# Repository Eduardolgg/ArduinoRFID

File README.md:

# ArduinoRFID
RFID authentication with Arduino.

# Domoticz

## Configuration

1. Set a static IP for the ESP-01s on your router.

2. Create the user variables rfid_id y rfid_ids_valid.
* rfid_id will contain the last tag sent to Domoticz.
* rfid_ids_valid will contain all valid tags.

3 Create the scripts using those found in the Domoticz_scripts directory, replace in the scripts the static IP associated with your wifi module.

## Add a new Tag

1. Scan the tag.

2. Go to Domoticz log and copy the ID.

3. Enter it in the user variable rfid_ids_valid by separating each Id by : (Ej: IDTAG1:IDTAG2:...).

# Arduino

1. Remember to replace the Domoticz IP and the user variable ID rfid_id in the code.

2. Flash Arduino and ESP-01s

3. Make the circuit using the included schemes

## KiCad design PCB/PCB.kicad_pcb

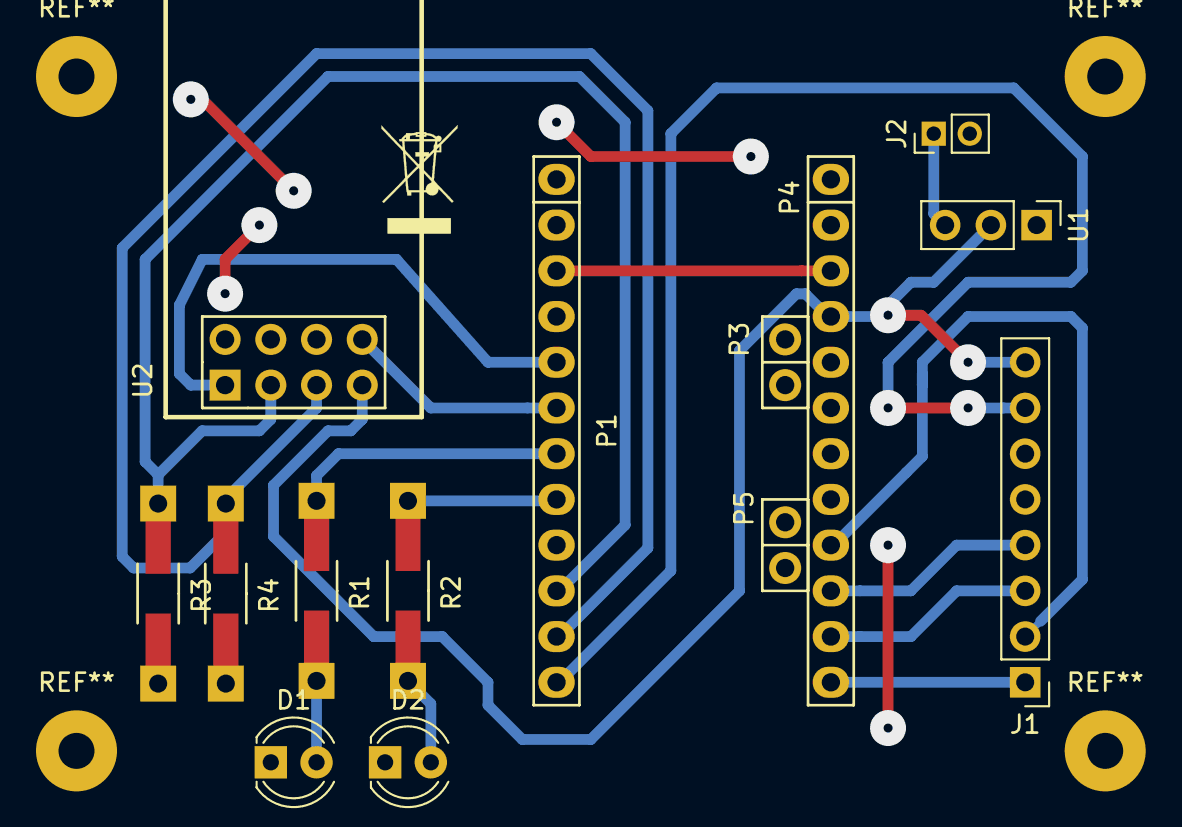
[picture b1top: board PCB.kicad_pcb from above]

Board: 2 copper layers, 14 parts (0 on the bottom side), 17 nets.

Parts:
D1, D2: LED; LED_D4.0mm
J1: Conn_01x08_Female - RFID-RC522; Socket_Strip_Straight_1x08_Pitch2.54mm
J2: Conn_01x02_Female_EntradaAlimentacion; Socket_Strip_Straight_1x02_Pitch2.00mm
P1: Digital; Socket_Strip_Arduino_1x12
P3, P5: ADC; Socket_Strip_Arduino_1x02
P4: Analog; Socket_Strip_Arduino_1x12
R1, R2: R; Resistor_SMD+THTuniversal_1206_RM10_HandSoldering
R3, R4: 10K; Resistor_SMD+THTuniversal_1206_RM10_HandSoldering
U1: AMS1117-3.3; Socket_Strip_Straight_1x03_Pitch2.54mm
U2: ESP-01v090; ESP-01

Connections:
+5V: J2.1, U1.3
/2: P1.5, U2.1
/3(**): P1.6, U2.8
/4: P1.7, R1.1
/5(**): P1.8, R2.1
/7: P1.10, R3.1, U2.3
/8: P1.11, R4.1, U2.5
/9(**): J1.7, P1.12
/10(**/SS): J1.1, P4.12
/11(**/MOSI): J1.3, P4.11
/12(MISO): J1.4, P4.10
/13(SCK): J1.2, P4.9
/Reset: P1.3, P4.3
GND: D1.1, D2.1, J1.6, J2.2, P1.4, P4.2, R3.2, R4.2, U1.1, U2.2
unnamed: D1.2, R1.2
unnamed: D2.2, R2.2
VCC: J1.8, P4.4, U1.2, U2.7

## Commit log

2020-03-01 Everything :)
